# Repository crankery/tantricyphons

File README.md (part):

# Tantricyphons

Tantricyphons is a Raspberry Pi Pico 2 based, monophonic vocal synthesizer module inspired by AudioNerdz's **Delay Lama**. It combines a formant-wave-function voice with MIDI, a dedicated pitch/gate/vowel interface, four assignable pots, four assignable CV inputs, and a small LCD showing the animated monk and setup menus.

The Pico runs the user interface and control acquisition on one core and audio synthesis on the other. PIO handles the DAC serial timing, external ADC transactions, and rotary encoder. DMA moves audio samples and LCD pixels without requiring the CPU to transmit individual bits or bytes.

**Current status:** firmware bring-up is working on a bare Pico 2, including the USB console, audio-buffer scheduling, and timing measurements. The module PCBs are in production. Analog audio output, converter accuracy, physical controls, and LCD operation on the assembled module still need board-level verification. This document describes the implemented design rather than claiming completed hardware qualification.

## Contents

- [Hardware organization](#hardware-organization)
- [Signals and pin assignments](#signals-and-pin-assignments)
- [Firmware architecture](#firmware-architecture)
- [Playing and control ownership](#playing-and-control-ownership)
- [Display and menus](#display-and-menus)
- [Calibration and saved settings](#calibration-and-saved-settings)
- [Build and upload](#build-and-upload)
- [USB console](#usb-console)
- [Debugging and timing](#debugging-and-timing)
- [Source-code map](#source-code-map)
- [Tests and bring-up](#tests-and-bring-up)
- [Credits and licensing](#credits-and-licensing)

## Hardware organization

The current electrical designs are under [`hw/main`](hw/main) and [`hw/control`](hw/control). The [`hw/fp`](hw/fp) directory contains the front-panel design, and [`hw/gerbers`](hw/gerbers) contains fabrication outputs. Open the board-specific KiCad projects when tracing the current circuits.

| Assembly | Main responsibilities | Design files |
| --- | --- | --- |
| Main board | Pico 2, MCP4821 DAC, MCP3208 ADC, 3.0 V references, reference buffering, power conversion, LCD and control-board connectors | [Schematic](hw/main/main.kicad_sch), [PCB](hw/main/main.kicad_pcb) |
| Control / I/O board | CV and gate jacks, pots, encoder and buttons, MIDI input receiver, analog input conditioning, audio output stage | [Schematic](hw/control/control.kicad_sch), [PCB](hw/control/control.kicad_pcb) |
| Front panel | Mechanical layout and panel artwork | [Front-panel files](hw/fp) |

### Power and references

The module uses the modular-synth power rails, with local low-voltage supplies for the digital electronics. The main-board LMR50410 provides local power conversion; the Pico uses its 3.3 V logic domain. The analog control circuitry includes TL074 op-amps and uses the analog supply rails.

Separate **LM4040C30 3.0 V references** serve the Pico ADC and external ADC domains. Reference buffering is provided on the main board. The two references are nominally the same voltage but have separate calibration records in firmware. Pico `ADC_VREF` is physical pin 35, and `AGND` is pin 33.

The GPIO signals listed below are logic-level connections after the module's input conditioning. The analog circuitry converts jack voltages to the ADC ranges and the gate comparator produces a logic signal.

### Audio output

The **MCP4821** is a single-channel 12-bit DAC. Firmware converts signed floating-point audio to 12-bit unsigned codes and sends a 16-bit command with active output and 1x gain (`0x3000 | sample`). The DAC uses its own internal 2.048 V reference. Its output passes to the control-board analog output circuitry and audio jack.

The DAC is write-only in this design: successful DMA completion proves that firmware transmitted data, not that the DAC is present or that the audio jack has the intended signal. Confirm actual waveform and output level on the assembled hardware.

### Analog inputs

There are **eleven acquired analog channels**:

| Converter channel | Physical control | Firmware behavior |
| --- | --- | --- |
| Pico ADC0 / GP26 | Frequency CV | Dedicated 1 V/oct pitch path |
| Pico ADC1 / GP27 | Vowel CV | Added to the dedicated vowel-pot position |
| Pico ADC2 / GP28 | Vowel pot | Dedicated vowel-position control |
| MCP3208 CH0–3 | Pots 1–4 | Independently assignable in the menu |
| MCP3208 CH4–7 | CV inputs 1–4 | Independently assignable in the menu |

The dedicated frequency and vowel CV circuits scale unipolar jack voltage by **0.6** before the ADC. Nominally, 0–5 V at those jacks becomes 0–3 V at the ADC. The assignable MCP CV circuits use an offset and gain: nominally **ADC voltage = 1.5 V + 0.3 × jack voltage**, accommodating a bipolar input range around zero. The pot signals are referenced to the buffered control reference.

The Pico ADC hardware performs single-shot conversions. A PIO state machine clocks the MCP3208 at **500 kHz**, using one 24-clock transaction per channel. Core 0 schedules and collects both converters without blocking for conversions. A complete eleven-channel scan is started no more often than once per millisecond; actual cadence also depends on main-loop service time.

Snapshots expose raw counts and calibrated 0–1 readings. Raw update callbacks identify the converter, channel and fresh 12-bit value. Acquisition itself does not assign external channels to voice parameters.

### Gate, MIDI and controls

- The gate jack is conditioned by an **LM393** comparator. The resulting Pico input is **active low**, with a pull-up. Firmware polls it without the button-style debounce delay.
- The **TRS MIDI input** uses the board's **6N138** receiver, then feeds UART1 RX at 31,250 baud. Jack wiring and signal conditioning are defined by the control schematic.
- Encoder A/B are counted continuously by PIO. The encoder's separate push switch is **OK**, and the separate pushbutton is **Back**. Those switches use pull-ups and 20 ms software debounce.
- The **240 × 320 ST7789 LCD** uses hardware SPI0 and DMA, with separate chip-select, D/C, reset and backlight signals.

## Signals and pin assignments

These are **GPIO numbers**. The physical Pico header pin is included to avoid confusing the two numbering systems.

| GPIO | Pico header pin | Signal | Owner |
| --- | --- | --- | --- |
| GP0 | 1 | Probe diagnostic TX | UART0 TX only |
| GP1 | 2 | LCD CS | Core 0 GPIO |
| GP2 | 4 | LCD SCK | SPI0 |
| GP3 | 5 | LCD MOSI / SDA label | SPI0 |
| GP4 | 6 | LCD D/C | Core 0 GPIO |
| GP5 | 7 | LCD reset | Core 0 GPIO |
| GP6 | 9 | LCD backlight | Core 0 GPIO, on/off |
| GP7 | 10 | MCP3208 CS | PIO1 |
| GP8 | 11 | MCP3208 CLK | PIO1 |
| GP9 | 12 | MCP3208 DIN | PIO1 |
| GP10 | 14 | MCP3208 DOUT | PIO1 |
| GP11 | 15 | MCP4821 CS | PIO0 |
| GP12 | 16 | MCP4821 SCK | PIO0 |
| GP13 | 17 | MCP4821 SDI | PIO0 |
| GP14 | 19 | MCP4821 LDAC | PIO0 |
| GP15 | 20 | Unused | — |
| GP16 | 21 | Encoder A | PIO2 |
| GP17 | 22 | Encoder B | PIO2 |
| GP18 | 24 | Encoder OK switch | Core 0 GPIO |
| GP19 | 25 | Back switch | Core 0 GPIO |
| GP20 | 26 | Gate, active low | Core 0 GPIO |
| GP21 | 27 | MIDI RX | UART1 |
| GP22 | 29 | Spare | — |
| GP26 | 31 | FREQ_CV / ADC0 | Pico ADC |
| GP27 | 32 | VOWEL_CV / ADC1 | Pico ADC |
| GP28 | 34 | VOWEL_POT / ADC2 | Pico ADC |
| GP25 | Onboard LED, not a header pin | Audio-loop heartbeat | Core 1 GPIO |

The active pin definitions live in the corresponding peripheral headers. Historical generic SPI/I2C definitions in `tantricyphons.h` are template leftovers, not the current peripheral pin map.

## Firmware architecture

```mermaid
flowchart LR
    CV[CV jacks and pots] --> ADC[Pico ADC and MCP3208 / PIO1]
    MIDI[TRS MIDI receiver] --> UART[UART1 MIDI parser]
    ENC[Encoder / PIO2 and buttons] --> UI[Menu and assignments]
    ADC --> C0[Core 0: CV combination and routing]
    UI --> C0
    UART --> Q[Source-tagged event queue]
    C0 --> Q
    Q --> C1[Core 1: MIDI/CV ownership and voice DSP]
    C1 --> RAM[Two DAC buffers in RAM]
    RAM --> DMA[DMA and DAC PIO0]
    DMA --> DAC[MCP4821 and analog audio output]
    C1 --> SNAP[Small voice/status snapshots]
    SNAP --> LCD[Monk/menu rendering and SPI0 DMA]
    UI --> LCD
    LCD --> TFT[240x320 LCD]
    USB[USB console] --> C0
    USB --> Q
    USB --> SAVE[Calibration and settings]
    UI --> SAVE
```

### Core 0: acquisition and interface

`main()` initializes the event queue, menu/defaults, saved settings, controls, MIDI, analog acquisition and audio core, then starts the display and console. Its loop services:

1. MIDI UART input.
2. Encoder and debounced buttons.
3. ADC scans and dedicated CV/pot combination.
4. Menu state and incremental LCD rendering.
5. Deferred settings saves.
6. Probe UART diagnostics and USB console input/output.

Core 0 never directly edits the live voice. It sends source-tagged events to a bounded, multicore-safe queue. Audio and status snapshots are copied under short locks. A queue overflow releases note ownership to recover from a potentially lost Note Off; fresh CV gate status can resume CV playing.

### Core 1: audio

Core 1 owns the voice and audio-buffer producer. For each free DAC buffer it processes events, updates control ownership, renders floating-point samples, applies level compensation/smoothing, packs DAC commands and submits the buffer.

The default is **44.1 kHz with 256 samples per buffer**, giving about **5.8 ms** per block. Events affect the next render boundary. The PIO clock-divider rounding produces about 44,104.7 samples/second at the 150 MHz system clock. The diagnostic budget uses the actual divider.

The voice uses overlapping formant-wave-function grains, vowel-interpolated formants, aspiration, vibrato, glide and an envelope. Exact-input caches reuse pitch conversion, vibrato scaling and unchanged grain waveforms. Grain triggers still accumulate the waveform at the original times.

The onboard LED toggles every 100 completed buffer fills, about once every 0.58 seconds at 44.1 kHz. It indicates progress through the audio loop; it is not an audio-output detector.

### DAC buffer ownership

Two 256-word DAC buffers cycle through **FREE → FILLING → READY → PLAYING → FREE**. Both initial buffers are rendered before playback starts.

PIO supplies the sample clock and CS/SCK/SDI/LDAC sequence. A single DMA channel, paced by PIO's TX DREQ, feeds complete buffers. Its completion interrupt releases the consumed RAM buffer and starts the next ready one. The joined PIO FIFO bridges the interrupt handoff.

A RAM buffer can be released once DMA has copied its final word into the FIFO, even though those final samples have not finished playing. The CPU never refills a DMA-owned buffer. If the producer falls behind, PIO finishes the queued samples and holds the last DAC output until a ready buffer arrives.

### Peripheral allocation

| Resource | Use |
| --- | --- |
| PIO0, one state machine | MCP4821 output, 256 PIO cycles per sample |
| PIO1, one state machine | MCP3208 serial transactions |
| PIO2, one state machine | Encoder state table and cumulative edge count |
| One DMA channel, IRQ1 on core 1 | DAC buffer transmission/completion |
| One DMA channel, polled on core 0 | LCD pixel transmission |
| SPI0 | LCD, initially 12.5 MHz |
| UART1 | MIDI input, 31,250 baud, 8N1 |
| UART0 TX | Probe diagnostics, 115,200 baud, 8N1 |
| USB CDC | Interactive console and SDK USB reset interface |

The encoder program is placed at PIO2 address zero because it uses computed jumps. It keeps a wrapping count in PIO while the CPU is busy; the CPU drains cumulative snapshots roughly once per millisecond. Four quadrature edges form one menu detent by default.

## Playing and control ownership

### Dedicated CV playing

Frequency CV and gate work without a menu assignment or MIDI connection. The nominal mapping is **1 V/oct**, with **MIDI note 36 / C2 as the 0 V target**. The current CV pitch and gate state remain tracked while MIDI is playing.

The dedicated vowel control is:

```text
pot_offset = 2 * calibrated_pot_position - 1
vowel = clamp(0.5 + 0.5 * pot_offset + 0.1 * vowel_cv_volts, 0, 1)
```

The pot's center is zero offset, which corresponds to the voice's midpoint vowel of 0.5. With zero CV, full left/center/right select 0/0.5/1. Positive vowel CV adds modulation: 1 V adds 0.1 and 5 V adds 0.5. This dedicated CV input is unipolar; its circuit cannot measure negative modulation like the offset MCP CV inputs can. Depth constants are in `vowel_controls.h`.

### MIDI

MIDI channel **1** is selected at build time in `midi.h`. Supported messages are:

| Message | Behavior |
| --- | --- |
| Note On / Off | Monophonic, last-note priority; releasing the newest held note restores the previous one |
| Note On with velocity zero | Note Off |
| Pitch wheel | Vowel, following the classic Delay Lama mapping |
| CC1 | Vibrato depth |
| CC5 | Glide |
| CC7 | Level |
| CC13 | Voice character |
| CC120 / CC123 / System Reset | Release MIDI notes and restore CV ownership |

The parser supports running status and interleaved real-time messages. SysEx and unsupported messages are ignored. Velocity is passed to the voice API, but the current voice implementation does not use it to scale amplitude. Delay/CC12, sustain-pedal behavior and active-sensing timeout handling are not implemented.

### MIDI priority and handback

- Held MIDI notes own pitch and gate. CV changes cannot retune or stop them.
- Releasing the final MIDI note restores the current CV pitch/gate pair: gate high resumes CV, gate low releases the voice.
- MIDI controller updates own only their parameter, for two seconds after its last MIDI update. Other panel controls continue working.
- ADC updates are cached during that ownership period. After expiry, a 100 ms ramp returns to the latest ADC value. Without an ADC source, the MIDI value remains.
- Among panel sources targeting the same parameter, the most recently changed source wins. External pitch assignments share the panel pitch with the dedicated frequency CV. No additive summing or soft takeover is implemented for generic assignments.

Unplugging MIDI during a held note does not manufacture a missing Note Off. `off` in the console releases the MIDI note stack while leaving the CV path available.

## Display and menus

The upper **240 × 224 pixels** show the monk; the lower **240 × 96 pixels** show setup menus. The existing artwork consists of 30 packed 120 × 112, 4-bit palette frames. Build tooling embeds them unchanged in flash, using **201,632 bytes** including the palette.

Core 0 expands one source row per main-loop pass into a reusable **107,520-byte RGB565 RAM buffer**, scaling each pixel 2×. DMA sends the selected image through SPI0. The same buffer is reused for menu redraws when no transfer owns it. CS stays asserted until both DMA and the SPI shifter finish. Unchanged frames/menu views are skipped.

At the initial SPI speed, a monk image takes about 69 ms to transmit, allowing roughly 14 frames/sec before other overhead. Active notes select frames 6–29 by vowel. Idle mode follows the hold/blink/shuffle sequence. Display startup delays use deadlines rather than sleeping through the control loop.

### Setup interaction

Turn the encoder to select an entry, press **OK** to enter/edit/accept, and use **Back** to cancel or move up. Setup contains:

- **Input assignments:** eight inputs, four rows per page; select an input and its destination.
- **ADC calibration:** select Pico ADC or MCP3208 and follow the voltage-capture prompts.
- **Save settings:** explicitly persist accepted changes.
- **Reset defaults:** restore unassigned external inputs and nominal calibration in RAM; save separately to retain the reset.

Destinations are Off, Pitch, Vowel, Voice, Vibrato, Vibrato rate, Glide, Aspiration, Level, Attack, Decay, Sustain and Release. Most destinations map calibrated 0–1 input to 0–1 parameter values. Generic Pitch spans MIDI notes 36–84; Attack/Decay span 0–2 seconds, and Release 0–4 seconds.

Small input fluctuations are suppressed and generic updates are rate-limited to one per input per 20 ms. Dedicated vowel updates have their own smaller change threshold and 5 ms rate limit. Encoder direction, detent behavior and debounce still need checking on the actual controls.

## Calibration and saved settings

Each converter has **one shared calibration**, applied to all of its channels. Calibration uses its reference jack's known conditioning to fit ADC-pin voltage:

| Menu choice | Apply reference voltage here | ADC voltage at jack 1 V / 4 V |
| --- | --- | --- |
| Pico ADC | FREQ CV, ADC0 | 0.6 V / 2.4 V |
| MCP3208 | CV 1, CH4 | 1.8 V / 2.7 V |

Apply a stable **1.000 V**, let it settle and press OK; repeat with **4.000 V**. Each capture averages the next 64 reference-channel readings. The wizard rejects noisy, near-rail, reversed or implausible captures. Review and accept to apply the new bank calibration, then choose **Save settings** to make it persistent.

A shared calibration corrects the converter/reference path as measured through that reference input; it does not individually characterize every channel's resistors. Snapshots retain raw 12-bit readings alongside corrected, clamped 0–1 values.

Settings contain all eight external assignments and both calibrations. They use two alternating 4 KiB sectors at flash offsets **0x3FE000 and 0x3FF000**, the last 8 KiB of the Pico 2's 4 MiB flash. A versioned 256-byte record contains a sequence number and CRC32. A save writes and verifies the alternate sector, retaining the previous valid record. Boot loads the newest valid record or defaults. Version 1 settings migrate with nominal MCP calibration; new saves use version 2.

Unchanged saves avoid writing flash. The build and runtime guard against firmware overlapping the reserved sectors. Normal firmware updates can preserve those sectors; a full-chip erase clears settings.

Saving deliberately permits a brief audio/control interruption. The SDK locks out core 1 and disables interrupts while flash is unavailable. Writes wait until display startup has completed and display DMA is idle. Audio DMA/PIO can drain and stall during that operation, then recover. Underruns associated with a save are expected.

## Build and upload

### Tools

- Raspberry Pi Pico SDK **2.3.1**.
- Arm GNU toolchain; the checked-in VS Code setup uses **15_2_Rel1**.
- CMake **3.13+**, Ninja or another supported generator, and Python 3.
- `picotool` for SDK output generation/upload; the VS Code setup uses **2.3.1**.
- Optional: Raspberry Pi Pico VS Code extension, Debug Probe/OpenOCD/GDB, and clang-format.

The CMake project imports an installed SDK and defaults to board `pico2`. The firmware includes its own packed artwork, so the MonkSynth submodule is useful for reference but is not a build dependency. Repository submodule configuration currently uses an SSH URL.

Run these commands from **`src/tantricyphons`**:

```sh
export PICO_SDK_PATH=/path/to/pico-sdk
cmake -S . -B build -G Ninja -DPICO_BOARD=pico2 -DCMAKE_BUILD_TYPE=Release
cmake --build build -j4
```

After renaming or moving the firmware directory, recreate `build/`; existing CMake caches contain absolute source paths.

Ensure the Arm compiler and build tools are available on PATH, or provide `PICO_TOOLCHAIN_PATH` / `CMAKE_MAKE_PROGRAM`. The VS Code extension's installed tool paths are already configured under `.vscode`.

| Build setting | Default | Purpose |
| --- | --- | --- |
| `PICO_BOARD` | `pico2` | RP2350, non-wireless board and direct onboard LED |
| `TANTRICYPHONS_SAMPLE_RATE` | `44100` | Nominal audio rate; integer 8000–48000 |
| `TANTRICYPHONS_USB_CONSOLE` | `ON` | USB CDC console and SDK USB reset support |
| `TANTRICYPHONS_AUDIO_DEBUG` | `ON` | Once-per-second probe UART summaries |
| `SAMPLE_BUFFER_SIZE` | `256` in `tantricyphons.h` | Audio block size; rebuild required |

44.1 kHz is the primary target. Alternative rates can be selected with `-DTANTRICYPHONS_SAMPLE_RATE=32000` or `22050`; preserve the matching ELF when debugging a different build. Source stepping may be easier with a Debug build, but remeasure timing at the optimization level used for playback.

Outputs are `build/tantricyphons.uf2` for BOOTSEL upload, `build/tantricyphons.elf` for source debugging, `build/tantricyphons.bin` for the flash payload, and the linker map for size inspection. UF2 packaging is roughly twice the payload size. ELF debug information is not all programmed into flash.

### Upload without a probe

Hold **BOOTSEL** while connecting USB. Release it when the **RP2350** drive appears, then copy `build/tantricyphons.uf2` to it. The board restarts into firmware. Once this USB-enabled firmware is running, the SDK reset interface also supports subsequent picotool/Run Project uploads. Hardware BOOTSEL remains the recovery path.

### Source debugging and probe logs

Connect the probe's SWD interface to Pico SWCLK/SWDIO/GND for breakpoints, memory/register inspection and flashing. For diagnostic text, connect **Pico GP0 → probe UART RX** and ground; leave probe TX disconnected because **GP1 is LCD CS**, not debug RX. Open the probe UART at **115200, 8N1, no flow control**.

The native Pico USB console is separate from that UART. The existing `.vscode` OpenOCD paths include `openocd.exe`; confirm the executable path for the host OS before using those debug tasks.

Breakpoints and flash saves disturb audio timing. Use the running console, counters and timing measurements to investigate real-time behavior without intentionally stopping the audio core.

## USB console

Connect with a live serial terminal such as minicom, or a serial monitor configured to send messages with **LF or CRLF**. **115200, 8N1, no flow control** is conventional; USB CDC is not paced by the selected UART baud. The console echoes input, so disable local echo. It greets with `tantricyphons USB console. Type help.`

```text
help
info
note 69
resetstats
status
adc
set vowel 0.7
set vibrato 0.2
off
connections
routes
assign 0 vibrato
cal
save
```

| Command | Purpose |
| --- | --- |
| `help` | Command syntax and parameter ranges |
| `info` | Board, clock, nominal rate, peripherals and settings state |
| `status` | Note/vowel state, audio counters, timings and worst-block context |
| `resetstats` | Clear the audio measurement window at the next buffer boundary, preserving playback |
| `connections` | Separate transmitter/acquisition activity from unverified external device presence |
| `adc` | All eleven raw/calibrated readings, scan sequence and age |
| `note NOTE [VELOCITY]` | MIDI-style test note, values 0–127, default velocity 100 |
| `off [NOTE]` | Release one or all MIDI notes; high CV gate can still play |
| `set PARAM VALUE` | MIDI-priority parameter update; two-second ownership and normal handback apply |
| `routes` | Show the eight external assignments |
| `assign INPUT TARGET` | Change an assignment in RAM; inputs 0–3 are pots, 4–7 are CV |
| `cal` | Inspect the two calibration records |
| `save` | Request persistence; inspect `info` for completion |

`set` parameters are `vowel`, `voice`, `vibrato`, `vib_rate`, `glide`, `aspiration`, `level`, `attack`, `decay`, `sustain` and `release`. Values are 0–1 except Attack/Decay 0–2 seconds and Release 0–4 seconds. Assignment targets additionally include `off` and `pitch`.

The console runs on core 0 with bounded input/output work, buffered replies and USB backpressure. It accepts lines up to 95 characters, supports backspace and Ctrl-C line cancellation, and rejects malformed/non-finite/out-of-range numbers. Closing the terminal does not automatically release a held test note. There is no command history or arbitrary memory access.

MCP4821 and the TX-only LCD wiring have no readback. MCP3208 transactions have no device ID/ACK. An absent ADC and grounded inputs can both produce zeros. `connections` reports evidence such as rail readings, MIDI traffic and GPIO/encoder activity without claiming a verified chip connection.

## Debugging and timing

The primary measurement is **worst-case buffer fill time**, not just its average. At 44.1 kHz, keep complete work below the approximately 5804 µs measured block budget.

| Field | Meaning |
| --- | --- |
| `blocks` | Buffers rendered/submitted in this measurement window |
| `A/B` | Completed DMA transfers for each RAM buffer |
| `late` | Next buffer was not ready when DMA finished; FIFO may still cover the delay |
| `underrun` | Observed sticky PIO TXSTALL episodes; real FIFO starvation, not a missing-sample count |
| `fill last/avg/max` | Message handling + rendering + packing/submission; excludes waiting for a free buffer |
| `slow` | Fill times exceeding the configured block budget |
| `messages/render/pack` | Per-stage timings; pack includes submission |
| `grains/builds` | Grain triggers versus actual waveform rebuilds |
| `worst fill phases` | Stage times and grain counts from the single worst-fill block |
| `stats window` | Increments when `resetstats` is serviced by core 1 |

Stage maxima can come from different blocks. A fresh reset leaves the note/envelope, voice caches and buffer ownership untouched. An in-flight DMA transfer may complete after the reset, so its completion belongs to the new window. Counter snapshots update after the next completed fill.

In bare-Pico testing at 150 MHz/44.1 kHz, one sustained-note run reported approximately **1836 µs average / 3240 µs maximum**, with zero late buffers, underruns or over-budget blocks over 38,207 rendered buffers. Additional modulation testing was reported around 3300 µs. These are observed bring-up results, not guarantees for every pitch or fully wired control workload.

The optimization's host comparison produced **356,580 byte-identical samples** across multiple rates and parameter/envelope changes. The firmware still needs combined hardware stress tests: pitch changes, vowel motion, menu redraws, MIDI traffic and analog-input noise. Floating unconnected inputs can change controls during a nominally steady note.

## Source-code map

```text
src/tantricyphons/
├── src/                 # C implementations
│   ├── app/             # Startup and main loop
│   ├── audio/           # Voice, rendering and ownership
│   ├── controls/        # ADC, CV, routing, calibration and physical controls
│   ├── midi/            # MIDI parser and UART transport
│   ├── display/         # LCD, monk and menu
│   ├── settings/        # Persistence policy, format and flash adapter
│   ├── diagnostics/     # USB console and probe logs
│   ├── hardware/        # DAC driver
│   └── messaging/       # Inter-core event queue
├── include/             # Matching subsystem directories and header contracts
├── pio/                 # DAC, ADC and encoder state-machine programs
├── assets/              # Packed artwork and notices
├── tests/               # Host tests and PIO simulations
└── tools/               # Asset generation, size guard and formatting
```

Includes name their subsystem, for example `#include "audio/voice.h"` and
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
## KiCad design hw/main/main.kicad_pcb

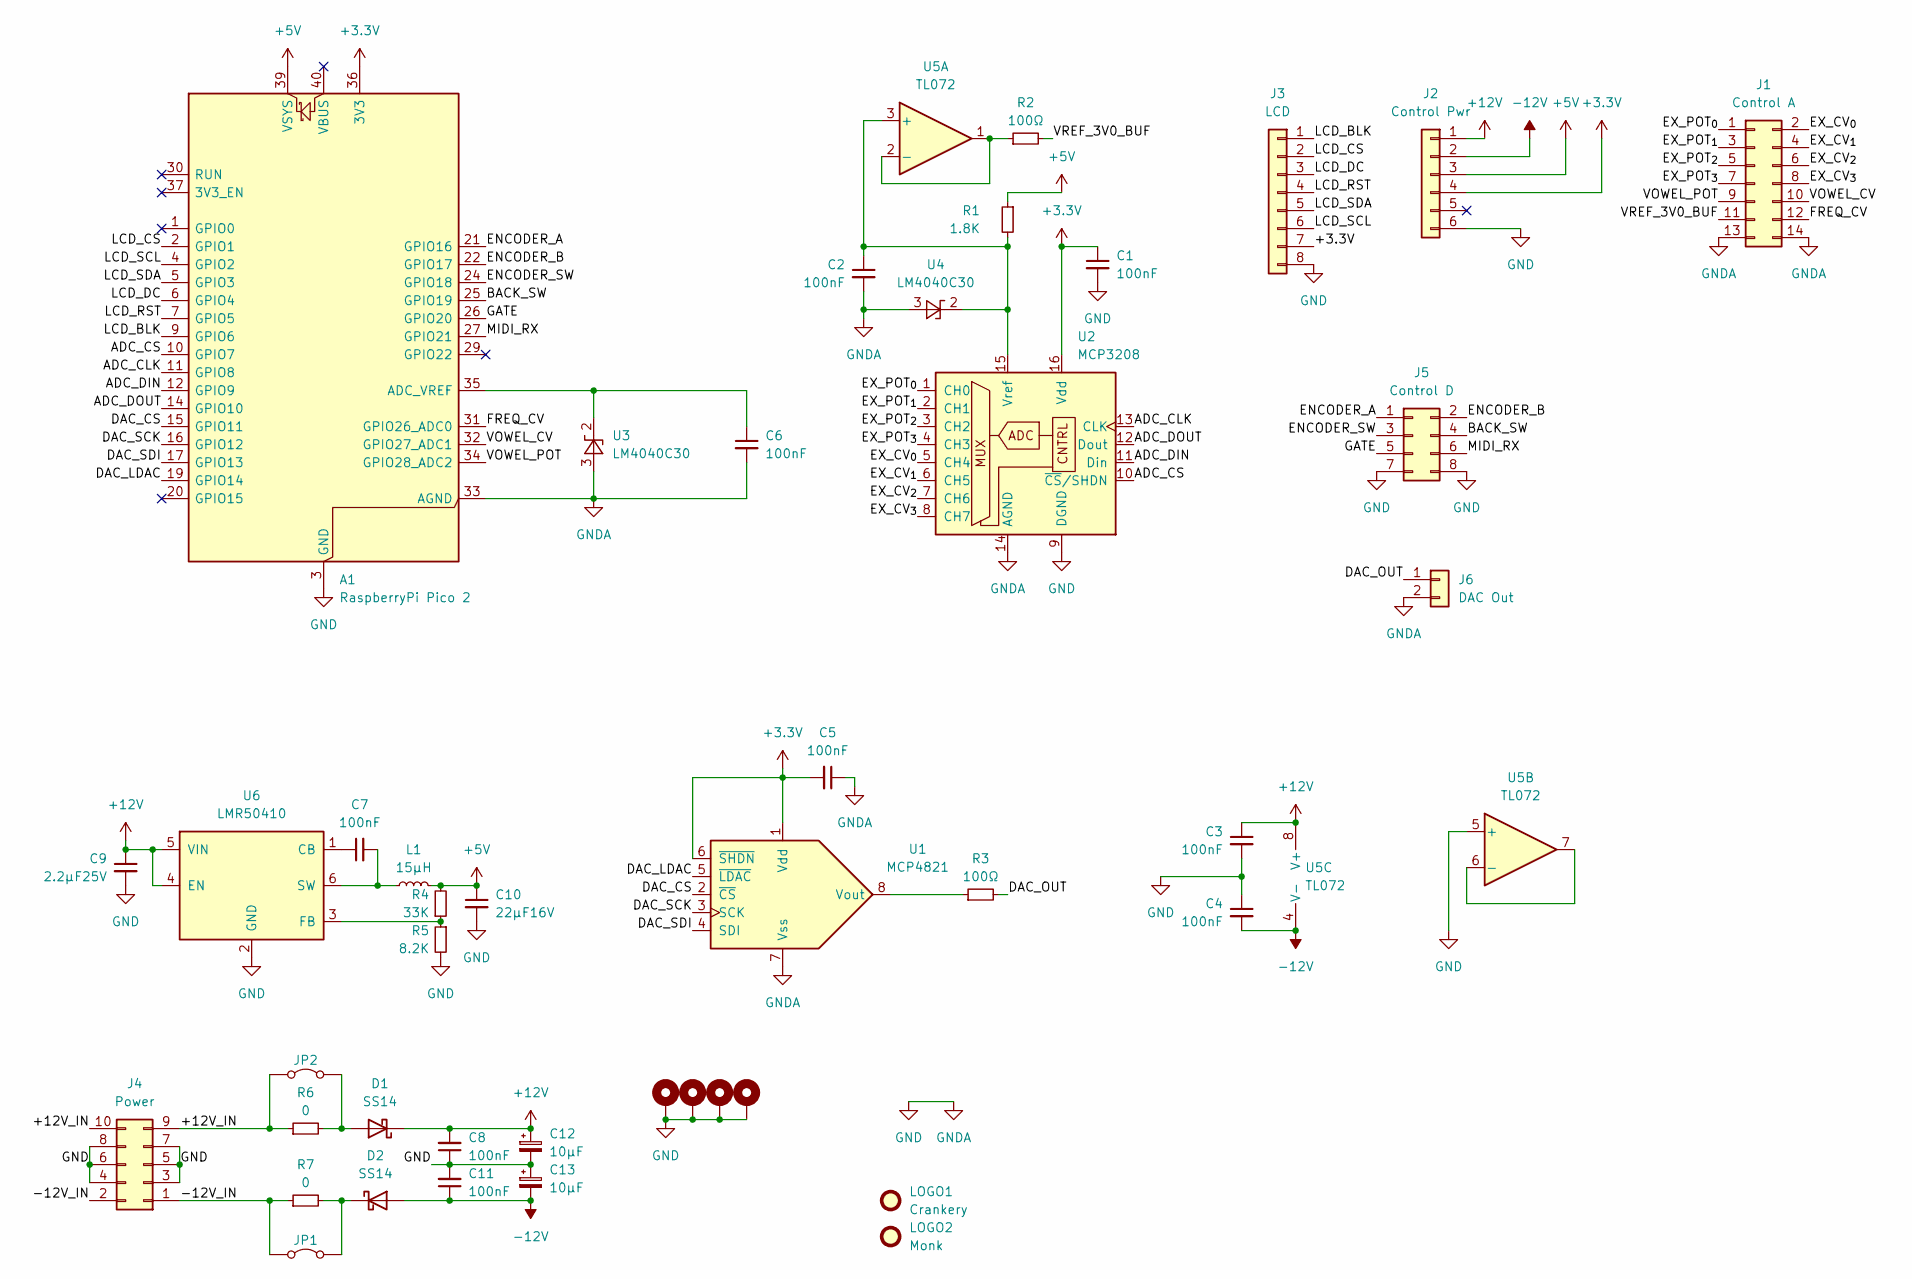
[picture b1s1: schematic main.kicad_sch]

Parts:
A1: RaspberryPi Pico 2; RaspberryPi_Pico_SMD
C1, C2, C3, C4, C5, C6, C8, C11: 100nF; C_Disc_D3.0mm_W1.6mm_P2.50mm
C7: 100nF; C_0805_2012Metric_Pad1.18x1.45mm_HandSolder
C9: 2.2µF25V; C_0805_2012Metric_Pad1.18x1.45mm_HandSolder
C10: 22µF16V; C_1210_3225Metric_Pad1.33x2.70mm_HandSolder
C12, C13: 10µF; CP_Radial_D6.3mm_P2.50mm
D1, D2: SS14; D_SMA
H1, H2, H3, H4: MountingHole_Pad; MountingHole_3.2mm_M3_DIN965_Pad
J1: Control A; PinSocket_2x07_P2.54mm_Vertical
J2: Control Pwr; PinSocket_1x06_P2.54mm_Vertical
J3: LCD; JST_PH_S8B-PH-K_1x08_P2.00mm_Horizontal
J4: Power; IDC-Header_2x05_P2.54mm_Horizontal
J5: Control D; PinSocket_2x04_P2.54mm_Vertical
J6: DAC Out; PinSocket_1x02_P2.54mm_Vertical
JP1, JP2: Jumper_2_Bridged; SolderJumper-2_P1.3mm_Bridged_RoundedPad1.0x1.5mm
L1: 15µH; L_TDK_VLS6045EX_VLS6045AF
LOGO1: Crankery; crankery_small
LOGO2: Monk; monk
R1: 1.8K; R_Axial_DIN0204_L3.6mm_D1.6mm_P5.08mm_Horizontal
R2, R3: 100Ω; R_Axial_DIN0204_L3.6mm_D1.6mm_P5.08mm_Horizontal
R4: 33K; R_0805_2012Metric_Pad1.20x1.40mm_HandSolder
R5: 8.2K; R_0805_2012Metric_Pad1.20x1.40mm_HandSolder
R6, R7: 0; R_Axial_DIN0204_L3.6mm_D1.6mm_P5.08mm_Horizontal
U1: MCP4821; DIP-8_W7.62mm
U2: MCP3208; DIP-16_W7.62mm
U3, U4: LM4040C30; TO-92_Inline
U5: TL072; DIP-8_W7.62mm
U6: LMR50410; SOT-23-6

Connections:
+3.3V: A1.36 (3V3), C1.1, C5.2, J2.4, J3.7, U1.1 (Vdd), U1.6 (~SHDN), U2.16 (Vdd)
+5V: A1.39 (VSYS), C10.1, J2.3, L1.2, R1.1, R4.2
+12V: C3.1, C8.2, C9.1, C12.1, D1.1 (K), J2.1, U5.8 (V+), U6.4 (EN), U6.5 (VIN)
-12V: C4.2, C11.1, C13.2, D2.2 (A), J2.2, U5.4 (V-)
/+12V_IN: J4.9, J4.10, JP2.1 (A), R6.1
/-12V_IN: J4.1, J4.2, JP1.1 (A), R7.1
/ADC_CLK: A1.11 (GPIO8), U2.13 (CLK)
/ADC_CS: A1.10 (GPIO7), U2.10 (~CS/SHDN)
/ADC_DIN: A1.12 (GPIO9), U2.11 (Din)
/ADC_DOUT: A1.14 (GPIO10), U2.12 (Dout)
/BACK_SW: A1.25 (GPIO19), J5.4
/DAC_CS: A1.15 (GPIO11), U1.2 (~CS)
/DAC_LDAC: A1.19 (GPIO14), U1.5 (~LDAC)
/DAC_OUT: J6.1, R3.2
/DAC_SCK: A1.16 (GPIO12), U1.3 (SCK)
/DAC_SDI: A1.17 (GPIO13), U1.4 (SDI)
/ENCODER_A: A1.21 (GPIO16), J5.1
/ENCODER_B: A1.22 (GPIO17), J5.2
/ENCODER_SW: A1.24 (GPIO18), J5.3
/EX_CV_{0}: J1.2, U2.5 (CH4)
/EX_CV_{1}: J1.4, U2.6 (CH5)
/EX_CV_{2}: J1.6, U2.7 (CH6)
/EX_CV_{3}: J1.8, U2.8 (CH7)
/EX_POT_{0}: J1.1, U2.1 (CH0)
/EX_POT_{1}: J1.3, U2.2 (CH1)
/EX_POT_{2}: J1.5, U2.3 (CH2)
/EX_POT_{3}: J1.7, U2.4 (CH3)
/FREQ_CV: A1.31 (GPIO26_ADC0), J1.12
/GATE: A1.26 (GPIO20), J5.5
/LCD_BLK: A1.9 (GPIO6), J3.1
/LCD_CS: A1.2 (GPIO1), J3.2
/LCD_DC: A1.6 (GPIO4), J3.3
/LCD_RST: A1.7 (GPIO5), J3.4
/LCD_SCL: A1.4 (GPIO2), J3.6
/LCD_SDA: A1.5 (GPIO3), J3.5
/MIDI_RX: A1.27 (GPIO21), J5.6
/VOWEL_CV: A1.32 (GPIO27_ADC1), J1.10
/VOWEL_POT: A1.34 (GPIO28_ADC2), J1.9
/VREF_3V0_BUF: J1.11, R2.2
GND: A1.3 (GND), A1.8 (GND), A1.13 (GND), A1.18 (GND), A1.23 (GND), A1.28 (GND), A1.33 (AGND), A1.38 (GND), C1.2, C2.2, C3.2, C4.1, C5.1, C6.2, C8.1, C9.2, C10.2, C11.2, C12.2, C13.1, H1.1 (1_1), H2.1 (1_1), H3.1 (1_1), H4.1 (1_1), J1.13, J1.14, J2.6, J3.8, J4.3, J4.4, J4.5, J4.6, J4.7, J4.8, J5.7, J5.8, J6.2, R5.2, U1.7 (Vss), U2.9 (DGND), U2.14 (AGND), U3.3 (A), U4.3 (A), U5.5 (+), U6.2 (GND)
unnamed: A1.35 (ADC_VREF), C6.1, U3.2 (K)
unnamed: D1.2 (A), JP2.2 (B), R6.2
unnamed: D2.1 (K), JP1.2 (B), R7.2
unnamed: R3.1, U1.8 (Vout)
unnamed: C2.1, R1.2, U2.15 (Vref), U4.2 (K), U5.3 (+)
unnamed: R2.1, U5.1, U5.2 (-)
unnamed: U5.6 (-), U5.7
unnamed: C7.1, U6.1 (CB)
unnamed: R4.1, R5.1, U6.3 (FB)
unnamed: C7.2, L1.1, U6.6 (SW)

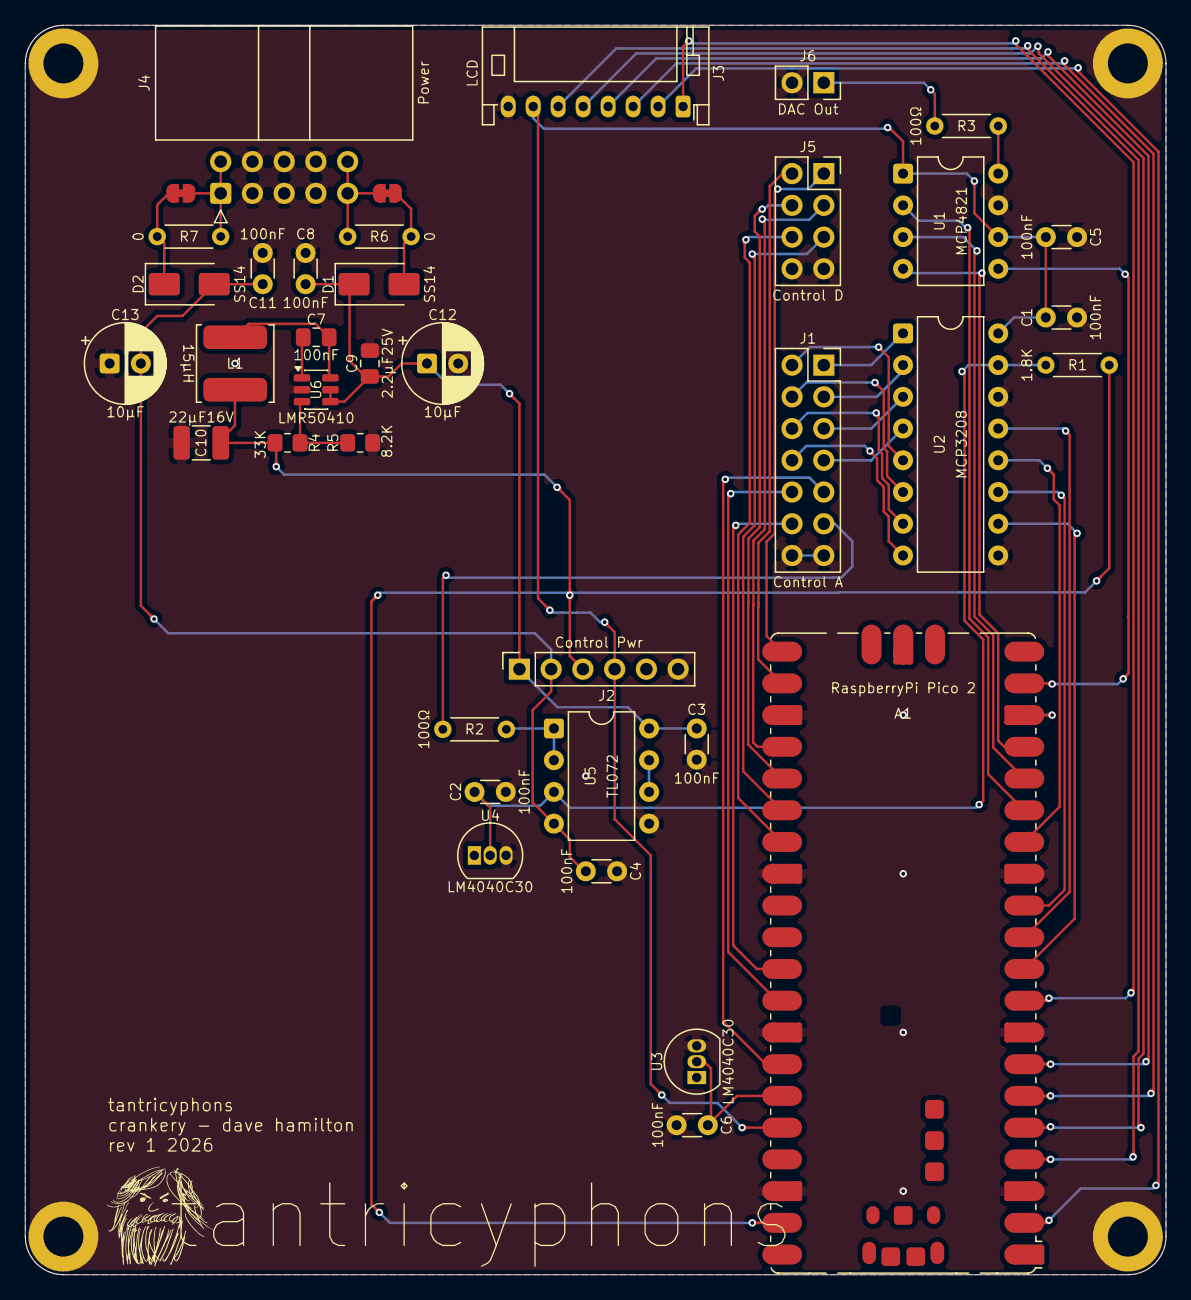
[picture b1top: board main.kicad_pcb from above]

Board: 2 copper layers, 91.3 x 100.0 mm, 44 parts (1 on the bottom side), 50 nets.

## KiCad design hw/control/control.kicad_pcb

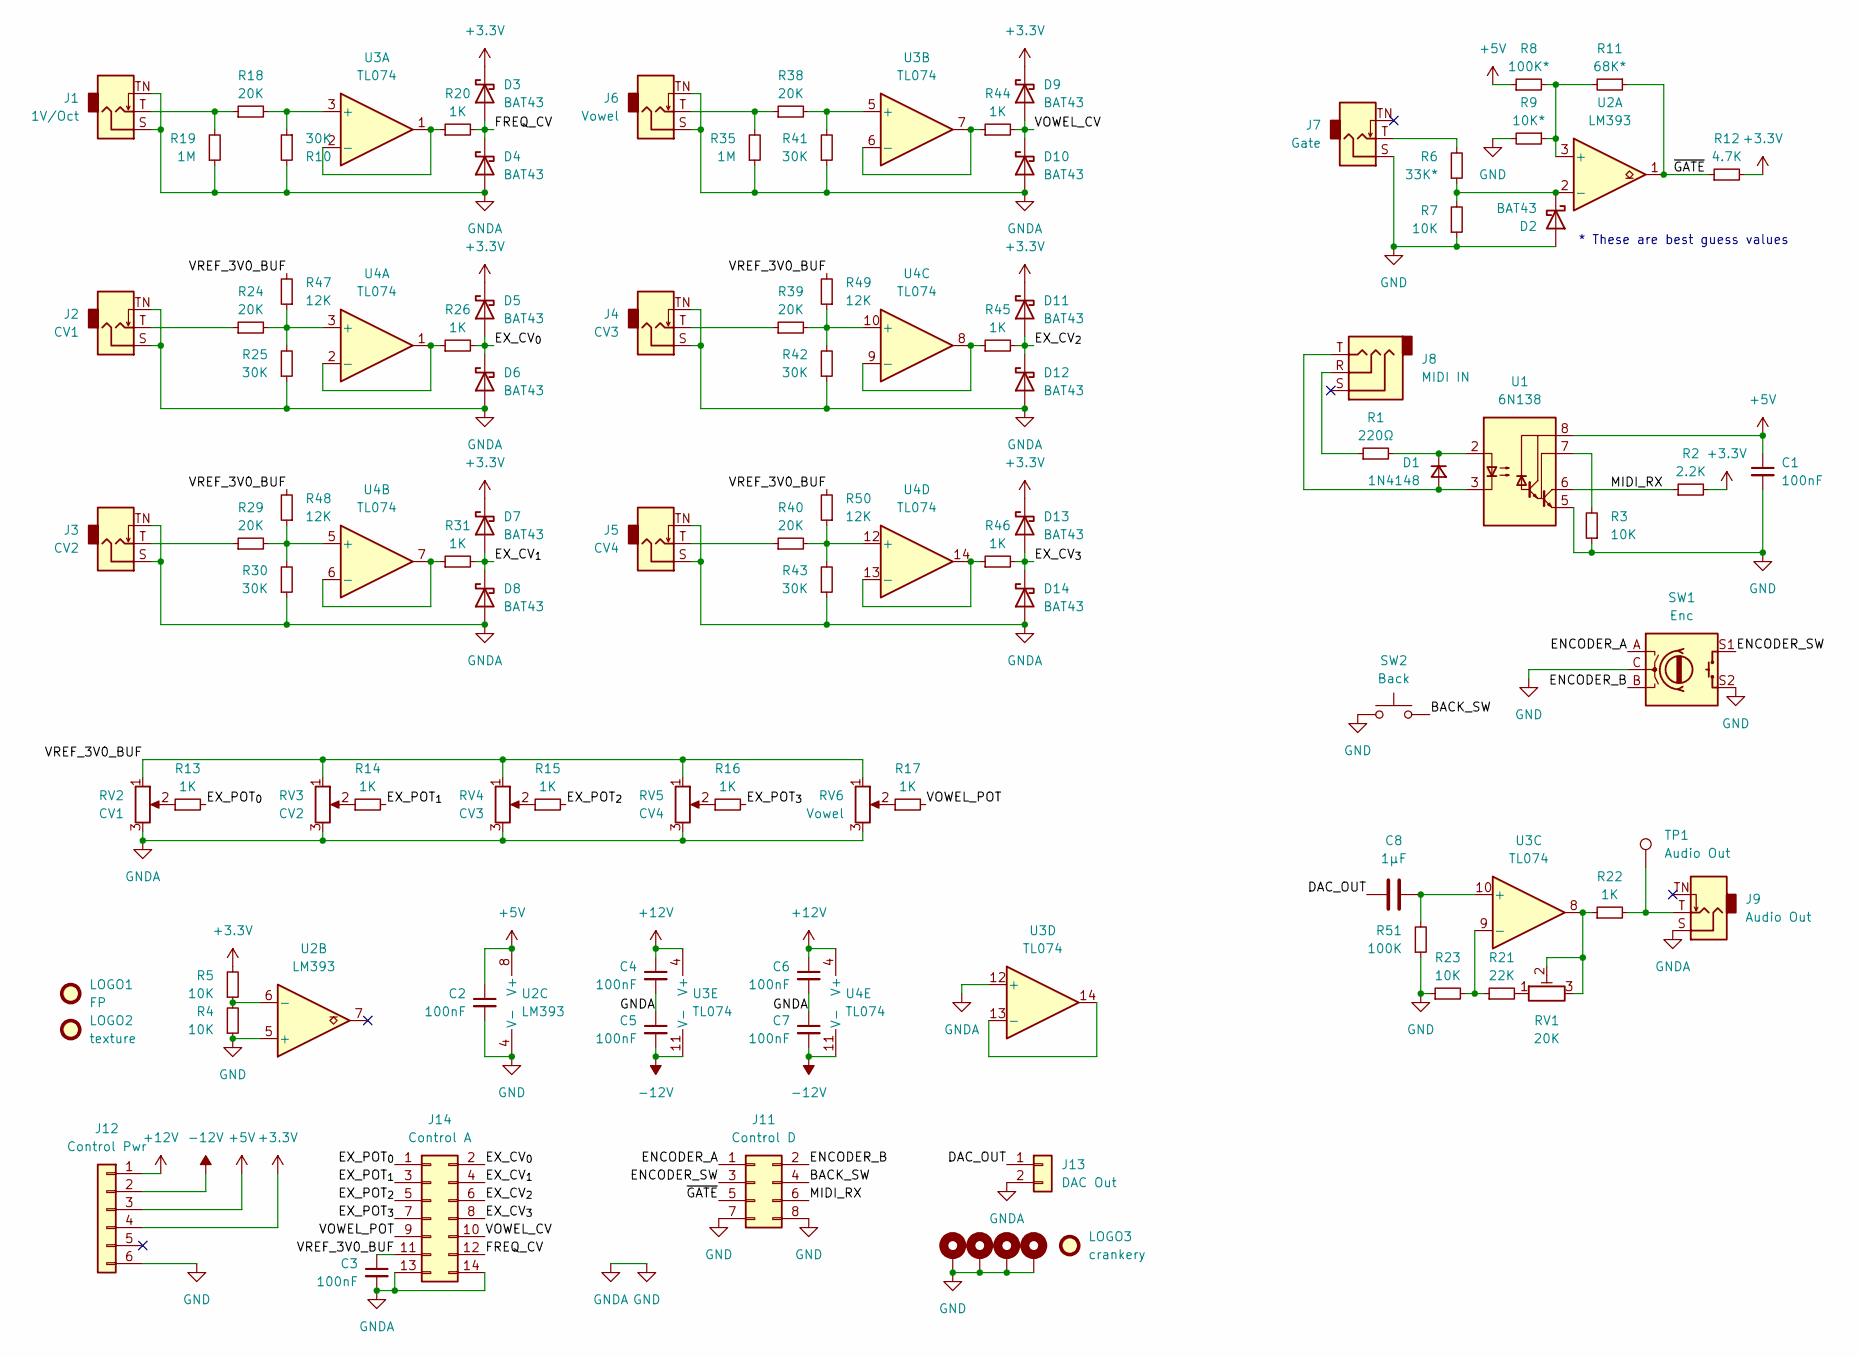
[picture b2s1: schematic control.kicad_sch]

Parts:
C1, C2, C3, C4, C5, C6, C7: 100nF; C_Disc_D3.0mm_W1.6mm_P2.50mm
C8: 1µF; C_Rect_L7.0mm_W2.5mm_P5.00mm
D1: 1N4148; D_DO-35_SOD27_P7.62mm_Horizontal
D2, D3, D4, D5, D6, D7, D8, D9, D10, D11, D12, D13, D14: BAT43; D_DO-35_SOD27_P7.62mm_Horizontal
H1, H2, H3, H4: MountingHole_Pad; MountingHole_3.2mm_M3_DIN965_Pad
J1: 1V/Oct; Jack_PJ398SM
J2: CV1; Jack_PJ398SM
J3: CV2; Jack_PJ398SM
J4: CV3; Jack_PJ398SM
J5: CV4; Jack_PJ398SM
J6: Vowel; Jack_PJ398SM
J7: Gate; Jack_PJ398SM
J8: MIDI IN; Jack_P419_GR
J9: Audio Out; Jack_PJ398SM
J11: Control D; PinHeader_2x04_P2.54mm_Vertical
J12: Control Pwr; PinHeader_1x06_P2.54mm_Vertical
J13: DAC Out; PinHeader_1x02_P2.54mm_Vertical
J14: Control A; PinHeader_2x07_P2.54mm_Vertical
LOGO1: FP; fp
LOGO2: texture; hammeredx
LOGO3: crankery; crankery_small
R1: 220Ω; R_Axial_DIN0204_L3.6mm_D1.6mm_P5.08mm_Horizontal
R2: 2.2K; R_Axial_DIN0204_L3.6mm_D1.6mm_P5.08mm_Horizontal
R3, R4, R5, R7, R23: 10K; R_Axial_DIN0204_L3.6mm_D1.6mm_P5.08mm_Horizontal
R6: 33K*; R_Axial_DIN0204_L3.6mm_D1.6mm_P5.08mm_Horizontal
R8: 100K*; R_Axial_DIN0204_L3.6mm_D1.6mm_P5.08mm_Horizontal
R9: 10K*; R_Axial_DIN0204_L3.6mm_D1.6mm_P5.08mm_Horizontal
R10, R25, R30, R41, R42, R43: 30K; R_Axial_DIN0204_L3.6mm_D1.6mm_P5.08mm_Horizontal
R11: 68K*; R_Axial_DIN0204_L3.6mm_D1.6mm_P5.08mm_Horizontal
R12: 4.7K; R_Axial_DIN0204_L3.6mm_D1.6mm_P5.08mm_Horizontal
R13, R14, R15, R16, R17, R20, R22, R26, R31, R44, R45, R46: 1K; R_Axial_DIN0204_L3.6mm_D1.6mm_P5.08mm_Horizontal
R18, R24, R29, R38, R39, R40: 20K; R_Axial_DIN0204_L3.6mm_D1.6mm_P5.08mm_Horizontal
R19, R35: 1M; R_Axial_DIN0204_L3.6mm_D1.6mm_P5.08mm_Horizontal
R21: 22K; R_Axial_DIN0204_L3.6mm_D1.6mm_P5.08mm_Horizontal
R47, R48, R49, R50: 12K; R_Axial_DIN0204_L3.6mm_D1.6mm_P5.08mm_Horizontal
R51: 100K; R_Axial_DIN0204_L3.6mm_D1.6mm_P5.08mm_Horizontal
RV1: 20K; Potentiometer_Runtron_RM-065_Vertical
RV2: CV1; Potentiometer_Alpha_RD901F-40-00D_Single_Vertical
RV3: CV2; Potentiometer_Alpha_RD901F-40-00D_Single_Vertical
RV4: CV3; Potentiometer_Alpha_RD901F-40-00D_Single_Vertical
RV5: CV4; Potentiometer_Alpha_RD901F-40-00D_Single_Vertical
RV6: Vowel; Potentiometer_Alpha_RD901F-40-00D_Single_Vertical
SW1: Enc; RotaryEncoder_Alps_EC11E-Switch_Vertical_H20mm
SW2: Back; SW_PUSH_6mm_H13mm
TP1: Audio Out; TestPoint_Pad_1.5x1.5mm
U1: 6N138; DIP-8_W7.62mm
U2: LM393; DIP-8_W7.62mm
U3, U4: TL074; DIP-14_W7.62mm

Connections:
+3.3V: D3.1 (K), D5.1 (K), D7.1 (K), D9.1 (K), D11.1 (K), D13.1 (K), J12.4, R2.2, R5.2, R12.2
+5V: C1.1, C2.1, J12.3, R8.1, U1.8 (VCC), U2.8 (V+)
+12V: C4.1, C6.1, J12.1, U3.4 (V+), U4.4 (V+)
-12V: C5.2, C7.2, J12.2, U3.11 (V-), U4.11 (V-)
/BACK_SW: J11.4, SW2.2
/DAC_OUT: C8.1, J13.1
/ENCODER_A: J11.1, SW1.A
/ENCODER_B: J11.2, SW1.B
/ENCODER_SW: J11.3, SW1.S1
/EX_CV_{0}: D5.2 (A), D6.1 (K), J14.2, R26.2
/EX_CV_{1}: D7.2 (A), D8.1 (K), J14.4, R31.2
/EX_CV_{2}: D11.2 (A), D12.1 (K), J14.6, R45.2
/EX_CV_{3}: D13.2 (A), D14.1 (K), J14.8, R46.2
/EX_POT_{0}: J14.1, R13.2
/EX_POT_{1}: J14.3, R14.2
/EX_POT_{2}: J14.5, R15.2
/EX_POT_{3}: J14.7, R16.2
/FREQ_CV: D3.2 (A), D4.1 (K), J14.12, R20.2
/MIDI_RX: J11.6, R2.1, U1.6 (VO2)
/VOWEL_CV: D9.2 (A), D10.1 (K), J14.10, R44.2
/VOWEL_POT: J14.9, R17.2
/VREF_3V0_BUF: C3.1, J14.11, R47.2, R48.2, R49.2, R50.2, RV2.1, RV3.1, RV4.1, RV5.1, RV6.1
/~GATE: J11.5, R11.1, R12.1, U2.1
GND: C1.2, C2.2, C3.2, C4.2, C5.1, C6.2, C7.1, D2.2 (A), D4.2 (A), D6.2 (A), D8.2 (A), D10.2 (A), D12.2 (A), D14.2 (A), H1.1 (1_1), H2.1 (1_1), H3.1 (1_1), H4.1 (1_1), J1.S, J1.TN, J2.S, J2.TN, J3.S, J3.TN, J4.S, J4.TN, J5.S, J5.TN, J6.S, J6.TN, J7.S, J9.S, J11.7, J11.8, J12.6, J13.2, J14.13, J14.14, R3.1, R4.1, R7.1, R9.2, R10.2, R19.1, R23.1, R25.1, R30.1, R35.1, R41.1, R42.1, R43.1, R51.1, RV2.3, RV3.3, RV4.3, RV5.3, RV6.3, SW1.C, SW1.S2, SW2.1, U1.5 (GND), U2.4 (V-), U2.5 (+), U3.12 (+)
unnamed: D1.2 (A), J8.T, U1.3 (C2)
unnamed: D1.1 (K), R1.2, U1.2 (C1)
unnamed: D2.1 (K), R6.1, R7.2, U2.2 (-)
unnamed: J1.T, R18.1, R19.2
unnamed: J2.T, R24.1
unnamed: J3.T, R29.1
unnamed: J4.T, R39.1
unnamed: J5.T, R40.1
unnamed: J6.T, R35.2, R38.1
unnamed: J7.T, R6.2
unnamed: J8.R, R1.1
unnamed: J9.T, R22.2, TP1.1 (1_1)
unnamed: R13.1, RV2.2
unnamed: R14.1, RV3.2
unnamed: R15.1, RV4.2
unnamed: R16.1, RV5.2
unnamed: R17.1, RV6.2
unnamed: R21.2, RV1.1
unnamed: R22.1, RV1.2, RV1.3, U3.8
unnamed: R3.2, U1.7 (VO1)
unnamed: R8.2, R9.1, R11.2, U2.3 (+)
unnamed: R4.2, R5.1, U2.6 (-)
unnamed: R10.1, R18.2, U3.3 (+)
unnamed: R20.1, U3.1, U3.2 (-)
unnamed: R38.2, R41.2, U3.5 (+)
unnamed: R44.1, U3.6 (-), U3.7
unnamed: C8.2, R51.2, U3.10 (+)
unnamed: R21.1, R23.2, U3.9 (-)
unnamed: U3.13 (-), U3.14
unnamed: R24.2, R25.2, R47.1, U4.3 (+)
unnamed: R26.1, U4.1, U4.2 (-)
unnamed: R29.2, R30.2, R48.1, U4.5 (+)
unnamed: R31.1, U4.6 (-), U4.7
unnamed: R39.2, R42.2, R49.1, U4.10 (+)
unnamed: R45.1, U4.8, U4.9 (-)
unnamed: R40.2, R43.2, R50.1, U4.12 (+)
unnamed: R46.1, U4.13 (-), U4.14

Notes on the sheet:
* These are best guess values

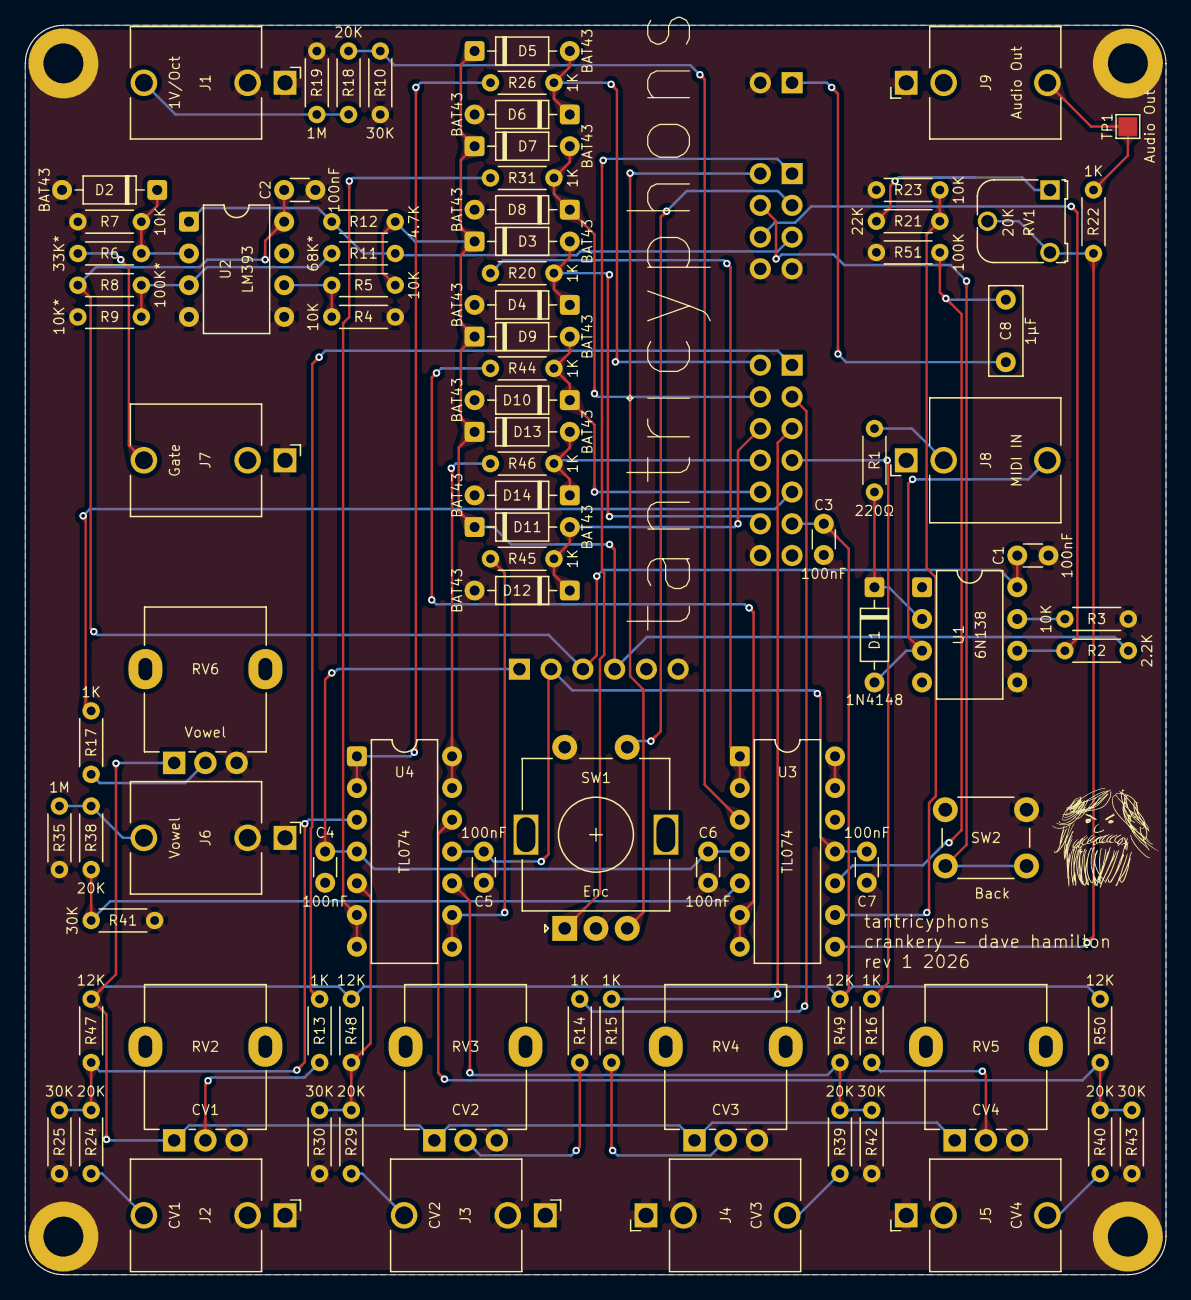
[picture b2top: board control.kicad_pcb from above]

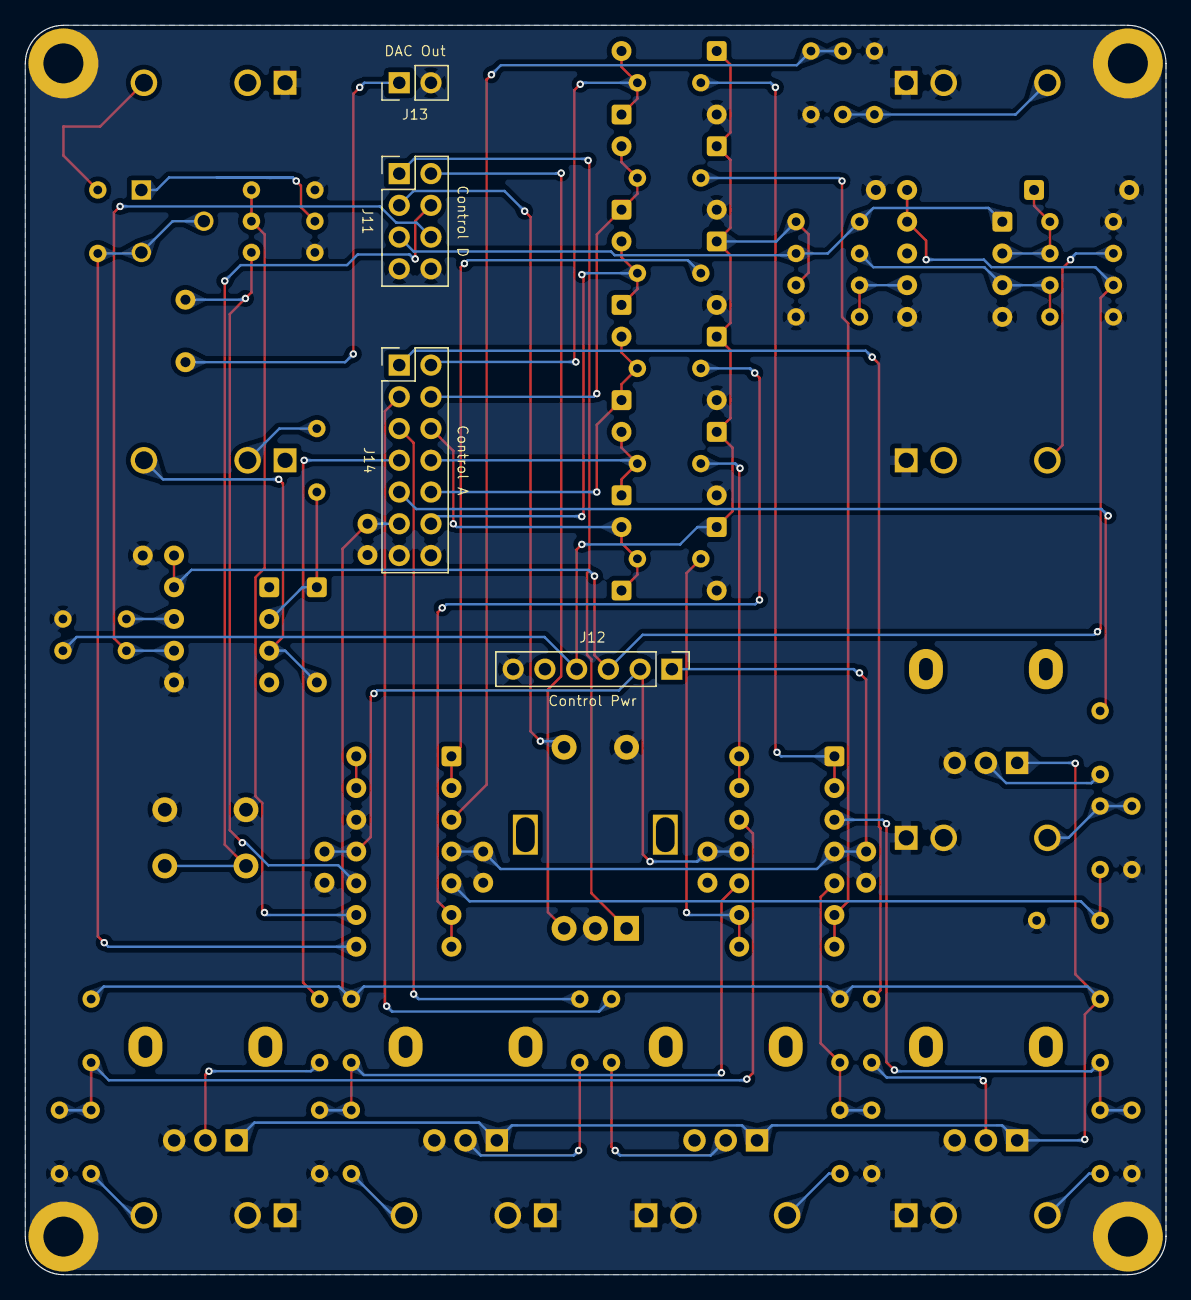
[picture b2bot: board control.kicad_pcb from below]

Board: 2 copper layers, 91.3 x 100.0 mm, 98 parts (4 on the bottom side), 61 nets.

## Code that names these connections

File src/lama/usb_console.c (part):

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        }

        append("; traffic is not a presence handshake\r\n"
               "GPIO levels: encoder A=%u B=%u OK=%u Back=%u Gate=%u\r\n"
               "Encoder edges=%" PRIu32
               "; idle/open contacts look alike (buttons/gate active low).\r\n"
               "Running firmware peripherals do not prove external chips are connected.\r\n",
               (unsigned)gpio_get(ENCODER_A),
               (unsigned)gpio_get(ENCODER_B),
               (unsigned)gpio_get(ENCODER_SW),
               (unsigned)gpio_get(BACK_SW),
               (unsigned)gpio_get(GATE_PIN),
               ui_controls_encoder_count());
        break;
    }
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
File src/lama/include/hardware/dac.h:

#ifndef LAMA_DAC_H
#define LAMA_DAC_H

#include <stdint.h>

#define DAC_CS 11
#define DAC_SCK 12
#define DAC_SDI 13
#define DAC_LDAC 14

typedef struct
{
    uint32_t starts[2], completions[2];
    uint32_t late_buffers; /* Next RAM buffer not ready at DMA completion */
    uint32_t underruns;    /* Observed PIO TXSTALL episodes; sticky/coalesced */
    uint32_t block_budget_us;
    int active_buffer; /* -1 when no DMA transfer is active */
} DacDebugStats;

/* Core 1 only; audio core republishes these for core 0. */
DacDebugStats dac_get_debug_stats(void);
/* Core 1 only: clear diagnostics, preserving live DMA/PIO/buffer ownership. */
void dac_reset_debug_stats(void);

/* All calls run on core 1. Acquire blocks until a buffer is free; submit
 * transfers ownership to DMA. Never write a buffer after submitting it. */
void dac_init(void);
uint16_t *get_free_dac_buffer(void);
void submit_dac_buffer(uint16_t *buffer);

#endif

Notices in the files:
README.md:
Credits and licensing:
- **Dave Hamilton:** Tantricyphons hardware and module project; see the repository [MIT license](LICENSE).
- **Jonathan Taylor / [MonkSynth](https://github.com/JonET/monksynth):** original C voice engine. `voice.c` and `voice.h` retain the copyright, full MIT notice and upstream attribution, with local adaptations described in their headers.
- **Xavier Rodet / IRCAM:** formant-wave-function synthesis technique, as credited by MonkSynth.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
